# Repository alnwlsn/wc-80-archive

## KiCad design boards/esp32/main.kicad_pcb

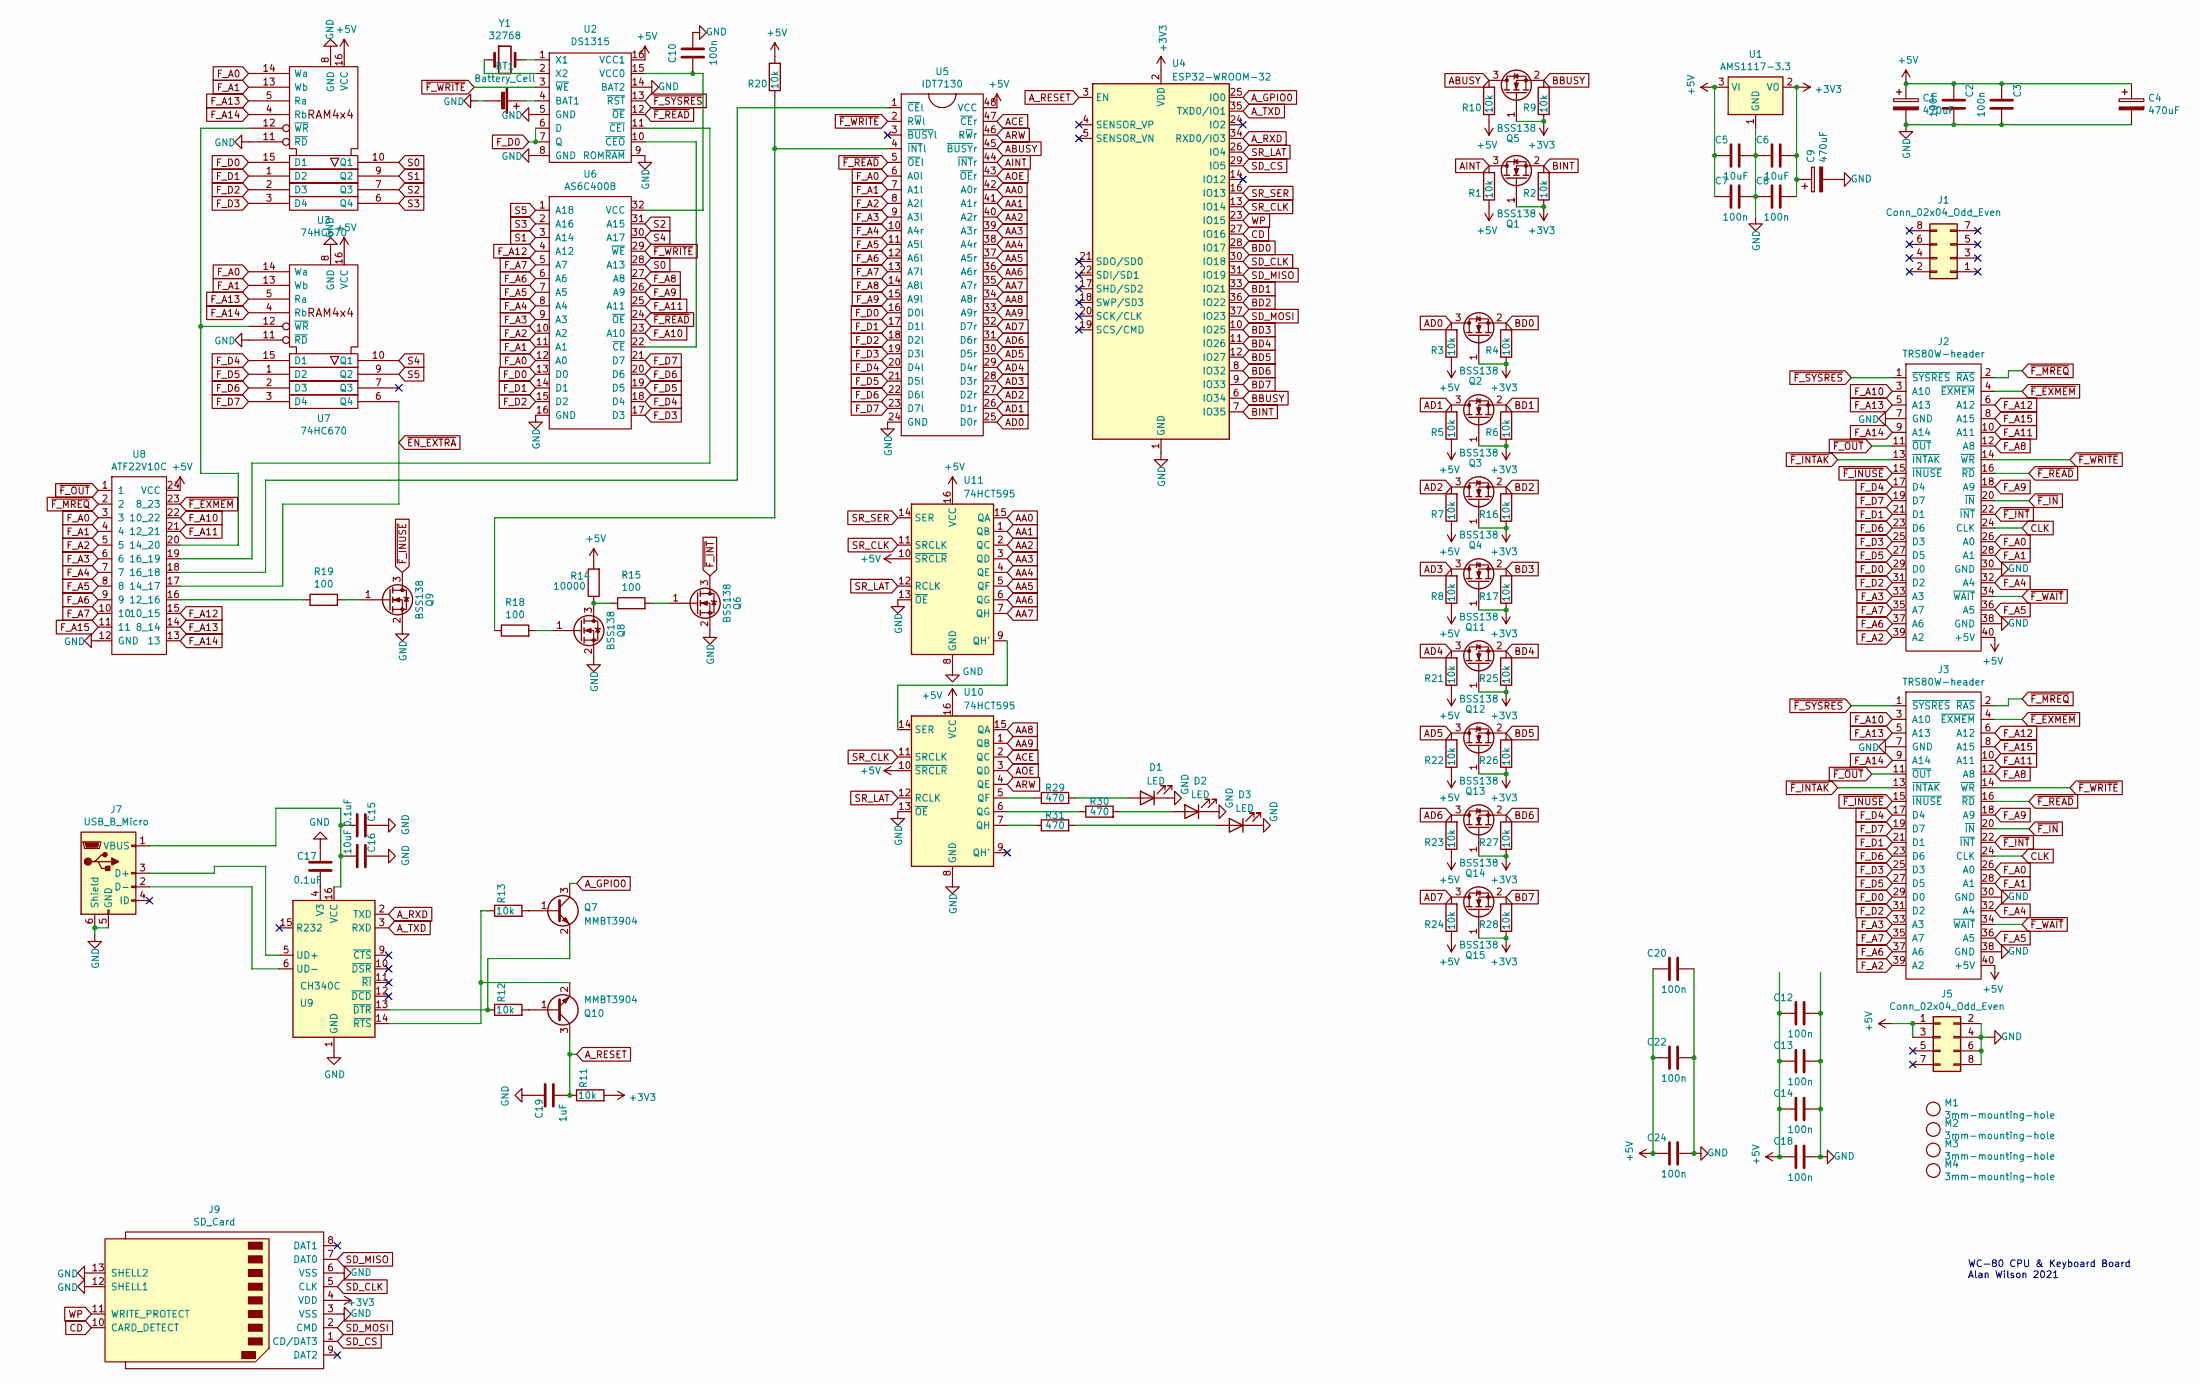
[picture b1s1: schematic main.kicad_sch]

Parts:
BT1: Battery_Cell; BS-01-A4CJ004
C1, C4, C9: 470uF; CP_Radial_D8.0mm_P3.50mm
C2, C3, C7, C8, C10, C12, C13, C14, C18, C20, C22, C24: 100n; C_0805_2012Metric
C5, C6, C16: 10uF; C_0805_2012Metric
C15, C17: 0.1uF; C_0805_2012Metric
C19: 1uF; C_0805_2012Metric
D1, D2, D3: LED; LED_D3.0mm
J1, J5: Conn_02x04_Odd_Even; PinHeader_2x04_P2.54mm_Vertical
J2, J3: TRS80W-header; PinHeader_2x20_P2.54mm_Vertical
J7: USB_B_Micro; USB_Micro-B_Molex-105017-0001
J9: SD_Card; SD_Card_ XUNPU_SD-101
M1, M2, M3, M4: 3mm-mounting-hole; MountingHole_3.2mm_M3_DIN965
Q1, Q2, Q3, Q4, Q5, Q6, Q8, Q9, Q11, Q12, Q13, Q14, Q15: BSS138; SOT-23
Q7, Q10: MMBT3904; SOT-23
R1, R2, R3, R4, R5, R6, R7, R8, R9, R10, R11, R12, R13, R16, R17, R20, R21, R22, R23, R24, R25, R26, R27, R28: 10k; R_0805_2012Metric
R14: 10000; R_0805_2012Metric
R15, R18, R19: 100; R_0805_2012Metric
R29, R30, R31: 470; R_0805_2012Metric
U1: AMS1117-3.3; SOT-223-3_TabPin2
U2: DS1315; DIP-16_W7.62mm_Socket
U3, U7: 74HC670; DIP-16_W7.62mm_Socket
U4: ESP32-WROOM-32
U5: IDT7130; DIP-48_W15.24mm_Socket
U6: AS6C4008; DIP-32_W15.24mm
U8: ATF22V10C; DIP-24_W7.62mm
U9: CH340C; SOIC-16_3.9x9.9mm_P1.27mm
U10, U11: 74HCT595; SO-16_3.9x9.9mm_P1.27mm
Y1: 32768; Crystal_AT310_D3.0mm_L10.0mm_Vertical

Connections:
+3V3: C6.2, C8.2, C9.1, J9.4 (VDD), Q1.1 (G), Q2.1 (G), Q3.1 (G), Q4.1 (G), Q5.1 (G), Q11.1 (G), Q12.1 (G), Q13.1 (G), Q14.1 (G), Q15.1 (G), R2.1, R4.1, R6.1, R9.1, R11.2, R16.1, R17.1, R25.1, R26.1, R27.1, R28.1, U1.2 (VO), U4.2 (VDD)
+5V: C1.1, C2.1, C3.1, C4.1, C5.1, C7.1, C12.1, C13.1, C14.1, C18.1, C20.1, C22.1, C24.1, J2.40 (+5V), J3.40 (+5V), J5.1, J5.3, R1.1, R3.1, R5.1, R7.1, R8.1, R10.1, R14.2, R20.2, R21.1, R22.1, R23.1, R24.1, U1.3 (VI), U2.16 (VCC1), U3.16 (VCC), U5.48 (VCC), U7.16 (VCC), U8.24 (VCC), U10.10 (~SRCLR), U10.16 (VCC), U11.10 (~SRCLR), U11.16 (VCC)
AA0: U5.42 (A0r), U11.15 (QA)
AA1: U5.41 (A1r), U11.1 (QB)
AA2: U5.40 (A2r), U11.2 (QC)
AA3: U5.39 (A3r), U11.3 (QD)
AA4: U5.38 (A4r), U11.4 (QE)
AA5: U5.37 (A5r), U11.5 (QF)
AA6: U5.36 (A6r), U11.6 (QG)
AA7: U5.35 (A7r), U11.7 (QH)
AA8: U5.34 (A8r), U10.15 (QA)
AA9: U5.33 (A9r), U10.1 (QB)
ABUSY: Q5.3 (D), R10.2, U5.45 (~BUSYr)
ACE: U5.47 (~CEr), U10.2 (QC)
AD0: Q2.3 (D), R3.2, U5.25 (D0r)
AD1: Q3.3 (D), R5.2, U5.26 (D1r)
AD2: Q4.3 (D), R7.2, U5.27 (D2r)
AD3: Q11.3 (D), R8.2, U5.28 (D3r)
AD4: Q12.3 (D), R21.2, U5.29 (D4r)
AD5: Q13.3 (D), R22.2, U5.30 (D5r)
AD6: Q14.3 (D), R23.2, U5.31 (D6r)
AD7: Q15.3 (D), R24.2, U5.32 (D7r)
AINT: Q1.3 (D), R1.2, U5.44 (~INTr)
AOE: U5.43 (~OEr), U10.3 (QD)
ARW: U5.46 (R~Wr), U10.4 (QE)
A_GPIO0: Q7.3 (C), U4.25 (IO0)
A_RESET: C19.1, Q10.3 (C), R11.1, U4.3 (EN)
A_RXD: U4.34 (RXD0/IO3), U9.2 (TXD)
A_TXD: U4.35 (TXD0/IO1), U9.3 (RXD)
BBUSY: Q5.2 (S), R9.2, U4.6 (IO34)
BD0: Q2.2 (S), R4.2, U4.28 (IO17)
BD1: Q3.2 (S), R6.2, U4.33 (IO21)
BD2: Q4.2 (S), R16.2, U4.36 (IO22)
BD3: Q11.2 (S), R17.2, U4.10 (IO25)
BD4: Q12.2 (S), R25.2, U4.11 (IO26)
BD5: Q13.2 (S), R26.2, U4.12 (IO27)
BD6: Q14.2 (S), R27.2, U4.8 (IO32)
BD7: Q15.2 (S), R28.2, U4.9 (IO33)
BINT: Q1.2 (S), R2.2, U4.7 (IO35)
CD: J9.10 (CARD_DETECT), U4.27 (IO16)
CLK: J2.24 (CLK), J3.24 (CLK)
F_A0: J2.26 (A0), J3.26 (A0), U3.14 (Wa), U5.6 (A0l), U6.12 (A0), U7.14 (Wa), U8.3
F_A1: J2.28 (A1), J3.28 (A1), U3.13 (Wb), U5.7 (A1l), U6.11 (A1), U7.13 (Wb), U8.4
F_A2: J2.39 (A2), J3.39 (A2), U5.8 (A2l), U6.10 (A2), U8.5
F_A3: J2.33 (A3), J3.33 (A3), U5.9 (A3l), U6.9 (A3), U8.6
F_A4: J2.32 (A4), J3.32 (A4), U5.10 (A4r), U6.8 (A4), U8.7
F_A5: J2.36 (A5), J3.36 (A5), U5.11 (A5l), U6.7 (A5), U8.8
F_A6: J2.37 (A6), J3.37 (A6), U5.12 (A6l), U6.6 (A6), U8.9
F_A7: J2.35 (A7), J3.35 (A7), U5.13 (A7l), U6.5 (A7), U8.10
F_A8: J2.12 (A8), J3.12 (A8), U5.14 (A8l), U6.27 (A8)
F_A9: J2.18 (A9), J3.18 (A9), U5.15 (A9l), U6.26 (A9)
F_A10: J2.3 (A10), J3.3 (A10), U6.23 (A10), U8.22 (10_22)
F_A11: J2.10 (A11), J3.10 (A11), U6.25 (A11), U8.21 (12_21)
F_A12: J2.6 (A12), J3.6 (A12), U6.4 (A12), U8.15 (10_15)
F_A13: J2.5 (A13), J3.5 (A13), U3.5 (Ra), U7.5 (Ra), U8.14 (8_14)
F_A14: J2.9 (A14), J3.9 (A14), U3.4 (Rb), U7.4 (Rb), U8.13
F_A15: J2.8 (A15), J3.8 (A15), U8.11
F_D0: J2.29 (D0), J3.29 (D0), U2.6 (D), U2.7 (Q), U3.15 (D1), U5.16 (D0l), U6.13 (D0)
F_D1: J2.21 (D1), J3.21 (D1), U3.1 (D2), U5.17 (D1l), U6.14 (D1)
F_D2: J2.31 (D2), J3.31 (D2), U3.2 (D3), U5.18 (D2l), U6.15 (D2)
F_D3: J2.25 (D3), J3.25 (D3), U3.3 (D4), U5.19 (D3l), U6.17 (D3)
F_D4: J2.17 (D4), J3.17 (D4), U5.20 (D4l), U6.18 (D4), U7.15 (D1)
F_D5: J2.27 (D5), J3.27 (D5), U5.21 (D5l), U6.19 (D5), U7.1 (D2)
F_D6: J2.23 (D6), J3.23 (D6), U5.22 (D6l), U6.20 (D6), U7.2 (D3)
F_D7: J2.19 (D7), J3.19 (D7), U5.23 (D7l), U6.21 (D7), U7.3 (D4)
GND: BT1.2 (-), C1.2, C2.2, C3.2, C4.2, C5.2, C6.1, C7.2, C8.1, C9.2, C10.2, C12.2, C13.2, C14.2, C15.2, C16.2, C17.2, C18.2, C19.2, C20.2, C22.2, C24.2, D1.1 (K), D2.1 (K), D3.1 (K), J2.7 (GND), J2.30 (GND), J2.38 (GND), J3.7 (GND), J3.30 (GND), J3.38 (GND), J5.2, J5.4, J5.6, J5.8, J7.5 (GND), J7.6 (Shield), J9.3 (VSS), J9.6 (VSS), J9.12 (SHELL1), J9.13 (SHELL2), Q6.2 (S), Q8.2 (S), Q9.2 (S), U1.1 (GND), U2.5 (GND), U2.8 (GND), U2.9 (ROM~RAM), U2.14 (BAT2), U3.8 (GND), U3.11 (~RD), U4.1 (GND), U4.15 (GND), U4.38 (GND), U4.39 (GND), U5.24 (GND), U6.16 (GND), U7.8 (GND), U7.11 (~RD), U8.12 (GND), U9.1 (GND), U10.8 (GND), U10.13 (~OE), U11.8 (GND), U11.13 (~OE)
unnamed: BT1.1 (+), U2.4 (BAT1)
unnamed: D1.2 (A), R29.2
unnamed: D2.2 (A), R30.2
unnamed: D3.2 (A), R31.2
unnamed: J7.3 (D+), U9.5 (UD+)
unnamed: J7.2 (D-), U9.6 (UD-)
unnamed: C15.1, C16.1, J7.1 (VBUS), U9.16 (VCC)
unnamed: Q6.1 (G), R15.2
unnamed: Q7.1 (B), R13.2
unnamed: Q7.2 (E), R12.1, U9.13 (~DTR)
unnamed: Q8.3 (D), R14.1, R15.1
unnamed: Q8.1 (G), R18.2
unnamed: Q9.1 (G), R19.2
unnamed: Q10.1 (B), R12.2
unnamed: Q10.2 (E), R13.1, U9.14 (~RTS)
unnamed: C10.1, U2.15 (VCC0), U6.32 (VCC)
unnamed: U2.1 (X1), Y1.2
unnamed: U2.2 (X2), Y1.1
unnamed: U2.11 (~CEI), U8.19 (16_19)
unnamed: U2.10 (~CEO), U6.22 (~CE)
unnamed: U3.12 (~WR), U7.12 (~WR), U8.20 (14_20)
unnamed: U5.1 (~CEl), U8.18 (16_18)
unnamed: R18.1, R20.1, U5.4 (~INTl)
unnamed: R19.1, U8.16 (12_16)
unnamed: C17.1, U9.4 (V3)
unnamed: R29.1, U10.5 (QF)
unnamed: R30.1, U10.6 (QG)
unnamed: R31.1, U10.7 (QH)
unnamed: U10.14 (SER), U11.9 (QH')
S0: U3.10 (Q1), U6.28 (A13)
S1: U3.9 (Q2), U6.3 (A14)
S2: U3.7 (Q3), U6.31 (A15)
S3: U3.6 (Q4), U6.2 (A16)
S4: U6.30 (A17), U7.10 (Q1)
S5: U6.1 (A18), U7.9 (Q2)
SD_CLK: J9.5 (CLK), U4.30 (IO18)
SD_CS: J9.1 (CD/DAT3), U4.29 (IO5)
SD_MISO: J9.7 (DAT0), U4.31 (IO19)
SD_MOSI: J9.2 (CMD), U4.37 (IO23)
SR_CLK: U4.13 (IO14), U10.11 (SRCLK), U11.11 (SRCLK)
SR_LAT: U4.26 (IO4), U10.12 (RCLK), U11.12 (RCLK)
SR_SER: U4.16 (IO13), U11.14 (SER)
WP: J9.11 (WRITE_PROTECT), U4.23 (IO15)
~EN_EXTRA: U7.6 (Q4), U8.17 (14_17)
~F_EXMEM: J2.4 (~EXMEM), J3.4 (~EXMEM), U8.23 (8_23)
~F_INTAK: J2.13 (~INTAK), J3.13 (~INTAK)
~F_INT: J2.22 (~INT), J3.22 (~INT), Q6.3 (D)
~F_INUSE: J2.15 (~INUSE), J3.15 (~INUSE), Q9.3 (D)
~F_IN: J2.20 (~IN), J3.20 (~IN)
~F_MREQ: J2.2 (~RAS), J3.2 (~RAS), U8.2
~F_OUT: J2.11 (~OUT), J3.11 (~OUT), U8.1
~F_READ: J2.16 (~RD), J3.16 (~RD), U2.12 (~OE), U5.5 (~OEl), U6.24 (~OE)
~F_SYSRES: J2.1 (~SYSRES), J3.1 (~SYSRES), U2.13 (~RST)
~F_WAIT: J2.34 (~WAIT), J3.34 (~WAIT)
~F_WRITE: J2.14 (~WR), J3.14 (~WR), U2.3 (~WE), U5.2 (R~Wl), U6.29 (~WE)

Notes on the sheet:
WC-80 CPU & Keyboard Board Alan Wilson 2021

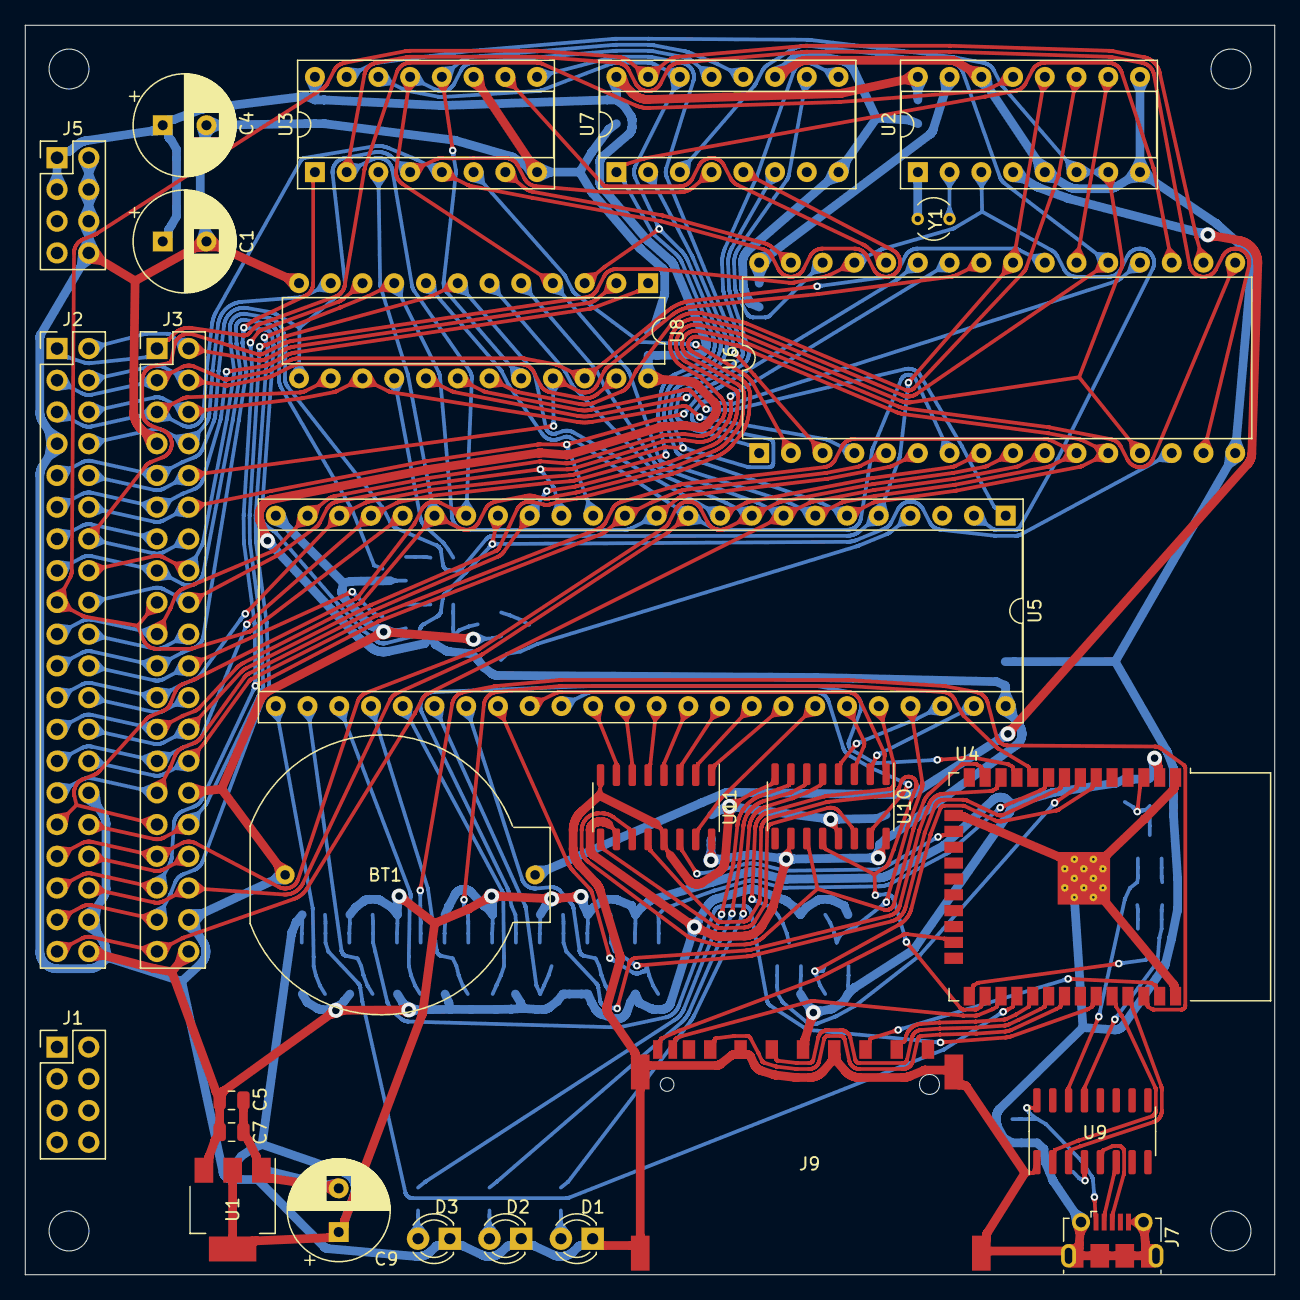
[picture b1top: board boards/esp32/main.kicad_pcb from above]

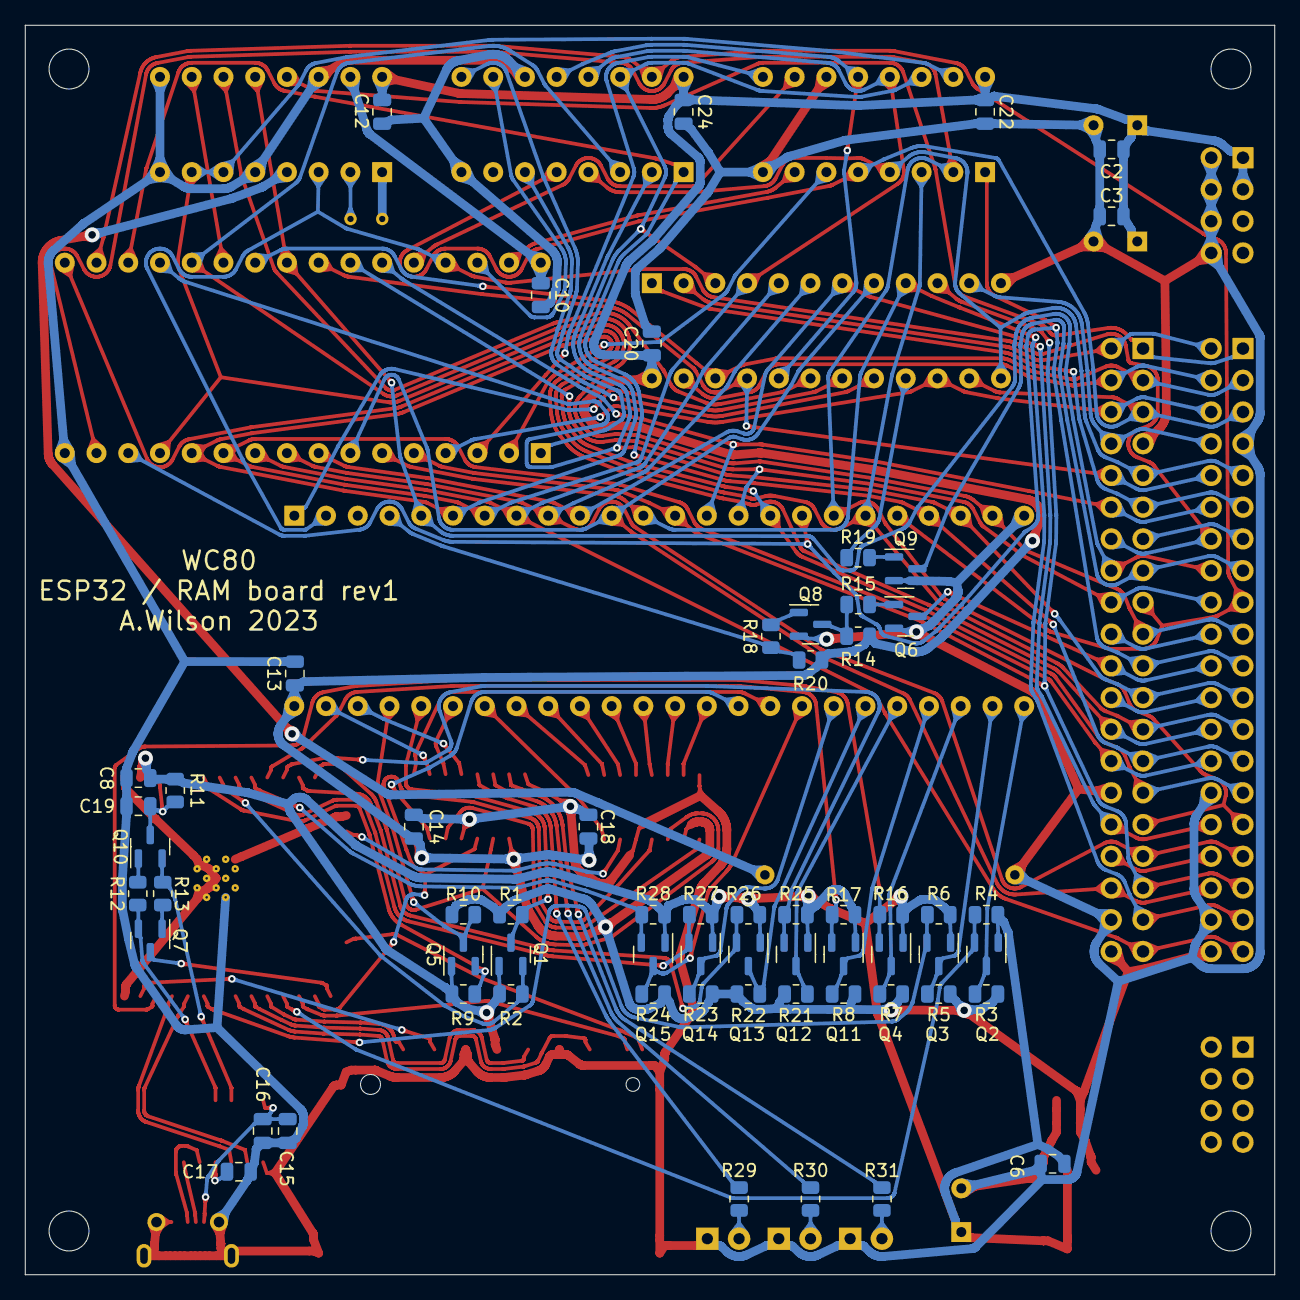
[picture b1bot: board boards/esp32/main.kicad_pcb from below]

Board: 2 copper layers, 100.0 x 100.0 mm, 93 parts (62 on the bottom side), 121 nets.
